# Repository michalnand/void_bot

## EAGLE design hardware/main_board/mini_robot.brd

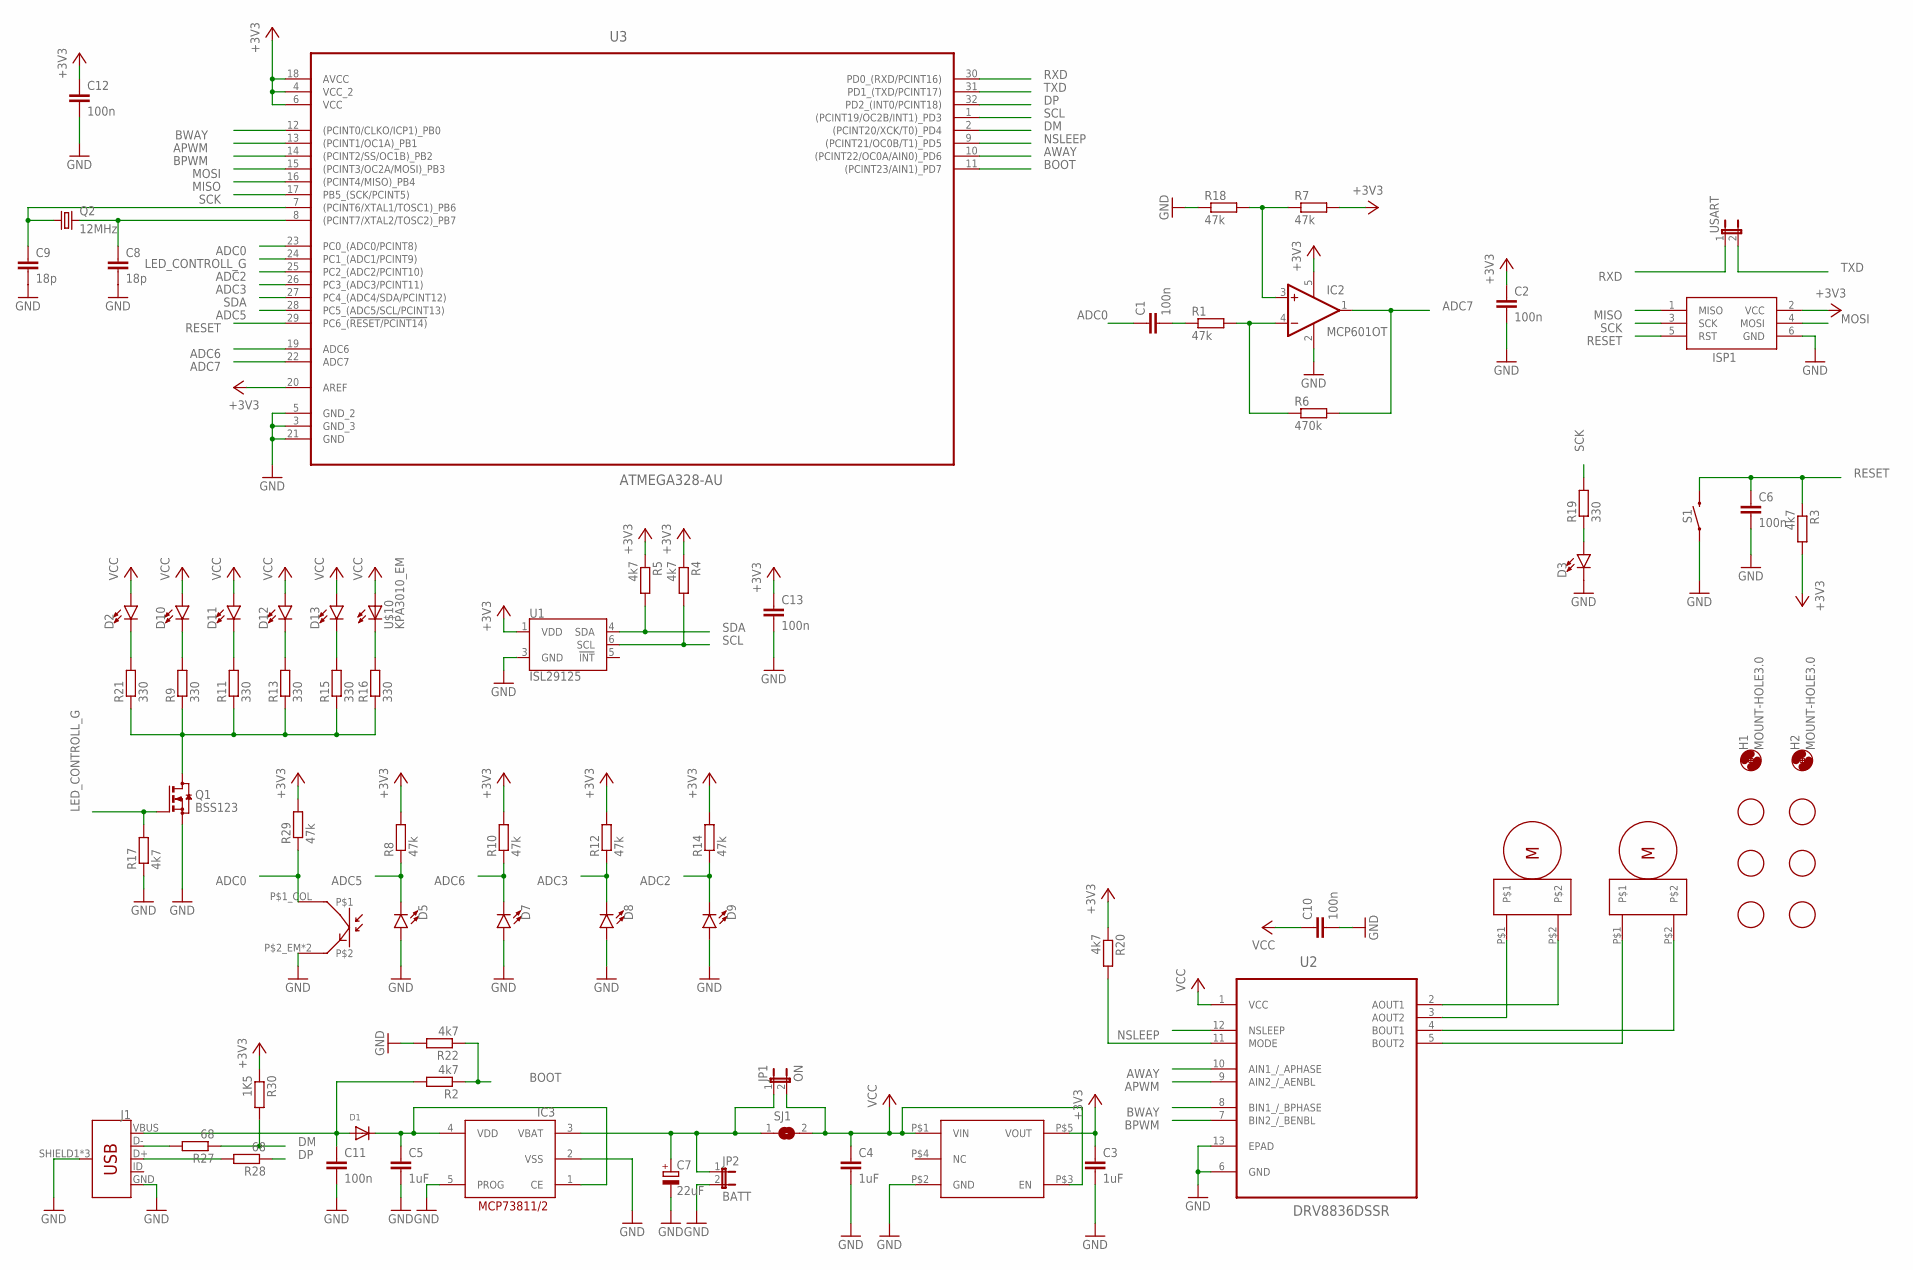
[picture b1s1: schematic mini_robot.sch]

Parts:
C1, C2, C6, C10, C11, C12, C13: 100n; C0603
C3, C4: 1uF; C0805
C5: 1uF; C0603
C7: 22uF; 153CLV-0505
C8, C9: 18p; C0603
D1: DIODE_SOD-123FL; SOD-123FL
D2, D3, D5, D7, D8, D9, D10, D11, D12, D13: LED-FKIT-1206; FKIT-LED-1206
H1, H2: MOUNT-HOLE3.0; 3,0
IC2: MCP601OT; SOT23-5
IC3: MCP73811/2; SOT23-5L
ISP1: AVRISP-6; AVRISP
J1: USB_MICRO-B_FEMALE-SMT; USB-B-MICRO-SMD
JP1: ON; JP1
JP2: BATT; JP1
Q1: BSS123; SOT23
Q2: 12MHz; CTS406
R1, R7, R8, R10, R12, R14, R18, R29: 47k; R0603
R2, R3, R4, R5, R17, R20, R22: 4k7; R0603
R6: 470k; R0603
R9, R11, R13, R15, R16, R19, R21: 330; R0603
R27, R28: 68; R0603
R30: 1K5; R0603
S1: MOMENTARY-SWITCH-SPST-SMD-6.2MM-TALL; TACTILE_SWITCH_SMD_6.2MM_TALL
SJ1: SJ
U1: ISL29125; ODFN-6
U2: DRV8836DSSR; SON50P200X300X80-13N
U3: ATMEGA328-AU; QFP80P900X900X120-32N
U$1, U$3, U$4, U$5, U$6, U$7: FIDUCIAL; FIDUCIAL_1MM
U$2: KPA3010
U$8, U$9: PLANETARY_GEAR_MOTOR
U$10: KPA3010_EM; KPA3010
U$11: MIC5504-3.3Y; SOT23-5
USART: JP1E; JP1

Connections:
+3V3: C2.1, C3.1, C12.1, C13.1, IC2.5 (V+), ISP1.2 (VCC), R3.2, R4.1, R5.1, R7.2, R8.2, R10.2, R12.2, R14.2, R20.1, R29.2, R30.1, U1.1 (VDD), U3.4 (VCC_2), U3.6 (VCC), U3.18 (AVCC), U3.20 (AREF), U$11.P$5 (VOUT)
ADC0: C1.1, R29.1, U3.23 (PC0_(ADC0/PCINT8)), U$2.P$1_COL
ADC2: D9.C, R14.1, U3.25 (PC2_(ADC2/PCINT10))
ADC3: D8.C, R12.1, U3.26 (PC3_(ADC3/PCINT11))
ADC5: D5.C, R8.1, U3.28 (PC5_(ADC5/SCL/PCINT13))
ADC6: D7.C, R10.1, U3.19 (ADC6)
ADC7: IC2.1 (OUT), R6.2, U3.22 (ADC7)
APWM: U2.9 (AIN2_/_AENBL), U3.13 ((PCINT1/OC1A)_PB1)
AWAY: U2.10 (AIN1_/_APHASE), U3.10 ((PCINT22/OC0A/AIN0)_PD6)
BOOT: R2.1, R22.1, U3.11 ((PCINT23/AIN1)_PD7)
BPWM: U2.7 (BIN2_/_BENBL), U3.14 ((PCINT2/SS/OC1B)_PB2)
BWAY: U2.8 (BIN1_/_BPHASE), U3.12 ((PCINT0/CLKO/ICP1)_PB0)
DM: R27.1, R30.2, U3.2 ((PCINT20/XCK/T0)_PD4)
DP: R28.1, U3.32 (PD2_(INT0/PCINT18))
GND: C2.2, C3.2, C4.2, C5.2, C6.2, C7.-, C8.2, C9.2, C10.2, C11.2, C12.2, C13.2, D3.C, D5.A, D7.A, D8.A, D9.A, IC2.2 (V-), IC3.2 (VSS), IC3.5 (PROG), ISP1.6 (GND), J1.GND, J1.SHIELD1 (SHIELD), J1.SHIELD2 (SHIELD), J1.SHIELD3 (SHIELD), JP2.2, Q1.2 (S), R17.1, R18.1, R22.2, S1.A2 (1), U1.3 (GND), U2.6 (GND), U2.13 (EPAD), U3.3 (GND_3), U3.5 (GND_2), U3.21 (GND), U$2.P$2_EM, U$2.P$3-NC, U$11.P$2 (GND)
LED_CONTROLL: Q1.3 (D), R9.1, R11.1, R13.1, R15.1, R16.1, R21.1
LED_CONTROLL_G: Q1.1 (G), R17.2, U3.24 (PC1_(ADC1/PCINT9))
MISO: ISP1.1 (MISO), U3.16 ((PCINT4/MISO)_PB4)
MOSI: ISP1.4 (MOSI), U3.15 ((PCINT3/OC2A/MOSI)_PB3)
unnamed: U2.2 (AOUT1), U$8.P$2
unnamed: U2.3 (AOUT2), U$8.P$1
unnamed: U2.4 (BOUT1), U$9.P$2
unnamed: U2.5 (BOUT2), U$9.P$1
unnamed: C11.1, D1.A, J1.VBUS, R2.2
unnamed: C5.1, D1.C, IC3.1 (CE), IC3.4 (VDD)
unnamed: C1.2, R1.1
unnamed: C7.+, IC3.3 (VBAT), JP1.1, JP2.1, SJ1.1
unnamed: R20.2, U2.11 (MODE)
unnamed: D10.C, R9.2
unnamed: D11.C, R11.2
unnamed: D12.C, R13.2
unnamed: D13.C, R15.2
unnamed: R16.2, U$10.P$1_COL (C)
unnamed: C8.1, Q2.3 (2), U3.8 ((PCINT7/XTAL2/TOSC2)_PB7)
unnamed: C9.1, Q2.1, U3.7 ((PCINT6/XTAL1/TOSC1)_PB6)
unnamed: D3.A, R19.1
unnamed: IC2.3 (+IN), R7.1, R18.2
unnamed: IC2.4 (-IN), R1.2, R6.1
unnamed: D2.C, R21.2
unnamed: J1.D-, R27.2
unnamed: J1.D+, R28.2
NSLEEP: U2.12 (NSLEEP), U3.9 ((PCINT21/OC0B/T1)_PD5)
RESET: C6.1, ISP1.5 (RST), R3.1, S1.B2 (2), U3.29 (PC6_(!RESET/PCINT14))
RXD: U3.30 (PD0_(RXD/PCINT16)), USART.1
SCK: ISP1.3 (SCK), R19.2, U3.17 (PB5_(SCK/PCINT5))
SCL: R4.2, U1.6 (SCL), U3.1 ((PCINT19/OC2B/INT1)_PD3)
SDA: R5.2, U1.4 (SDA), U3.27 (PC4_(ADC4/SDA/PCINT12))
TXD: U3.31 (PD1_(TXD/PCINT17)), USART.2
VCC: C4.1, C10.1, D2.A, D10.A, D11.A, D12.A, D13.A, JP1.2, SJ1.2, U2.1 (VCC), U$10.P$2_EM (A), U$10.P$3-NC (A), U$11.P$1 (VIN), U$11.P$3 (EN)

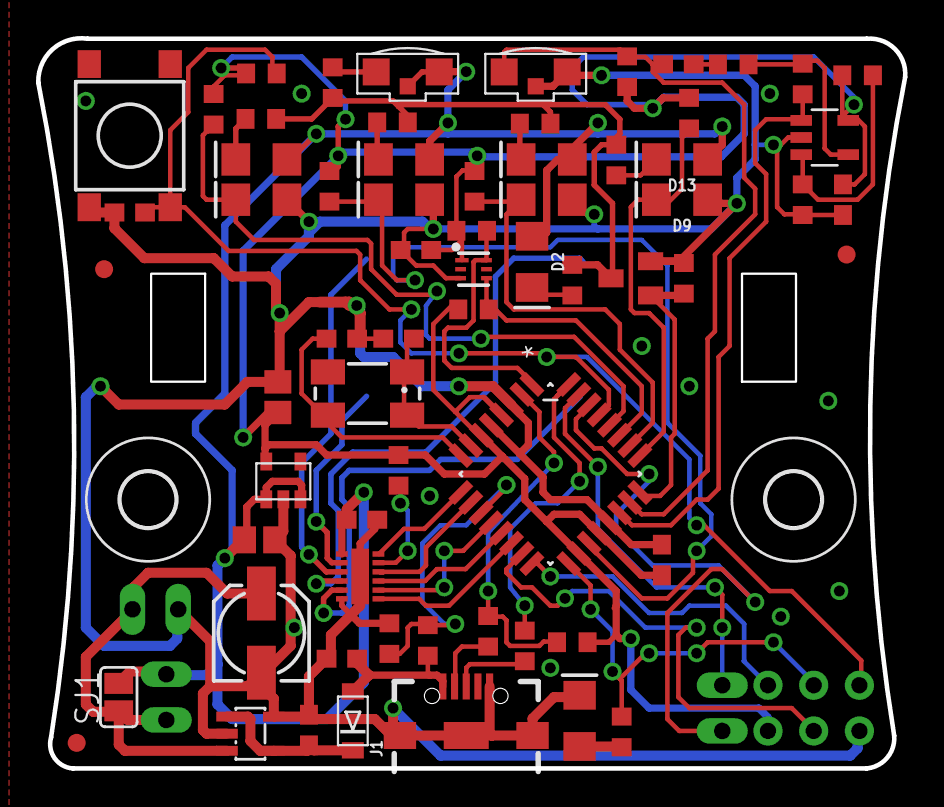
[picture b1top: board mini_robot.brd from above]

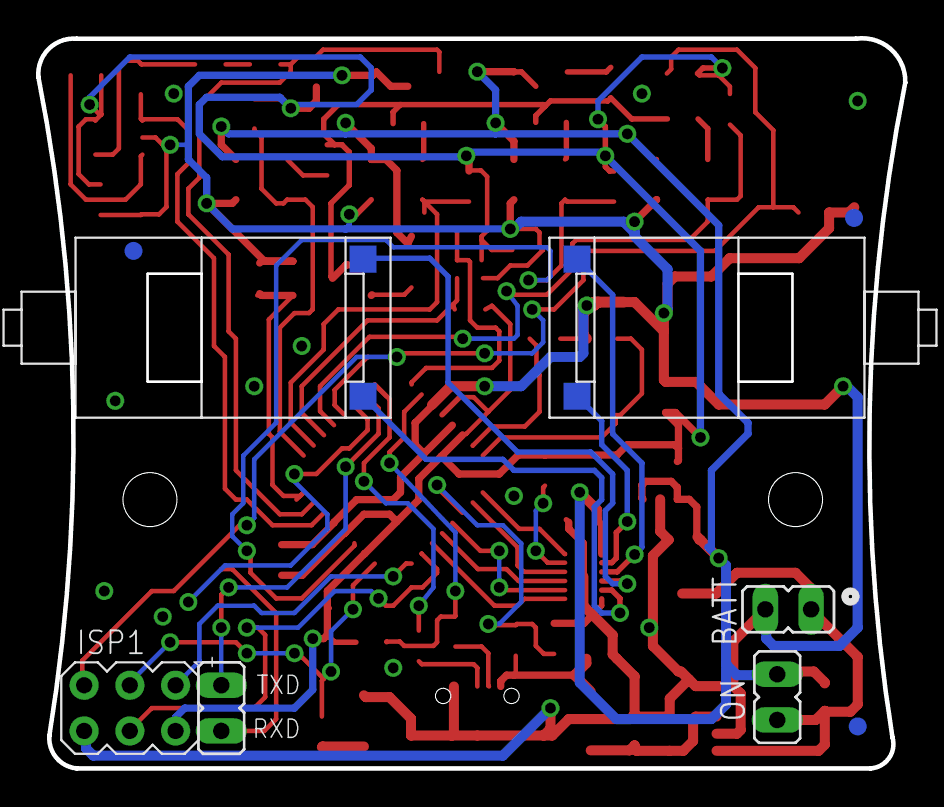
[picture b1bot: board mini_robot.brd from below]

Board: 2 copper layers, 48.2 x 40.6 mm, 77 parts (9 on the bottom side), 49 nets.

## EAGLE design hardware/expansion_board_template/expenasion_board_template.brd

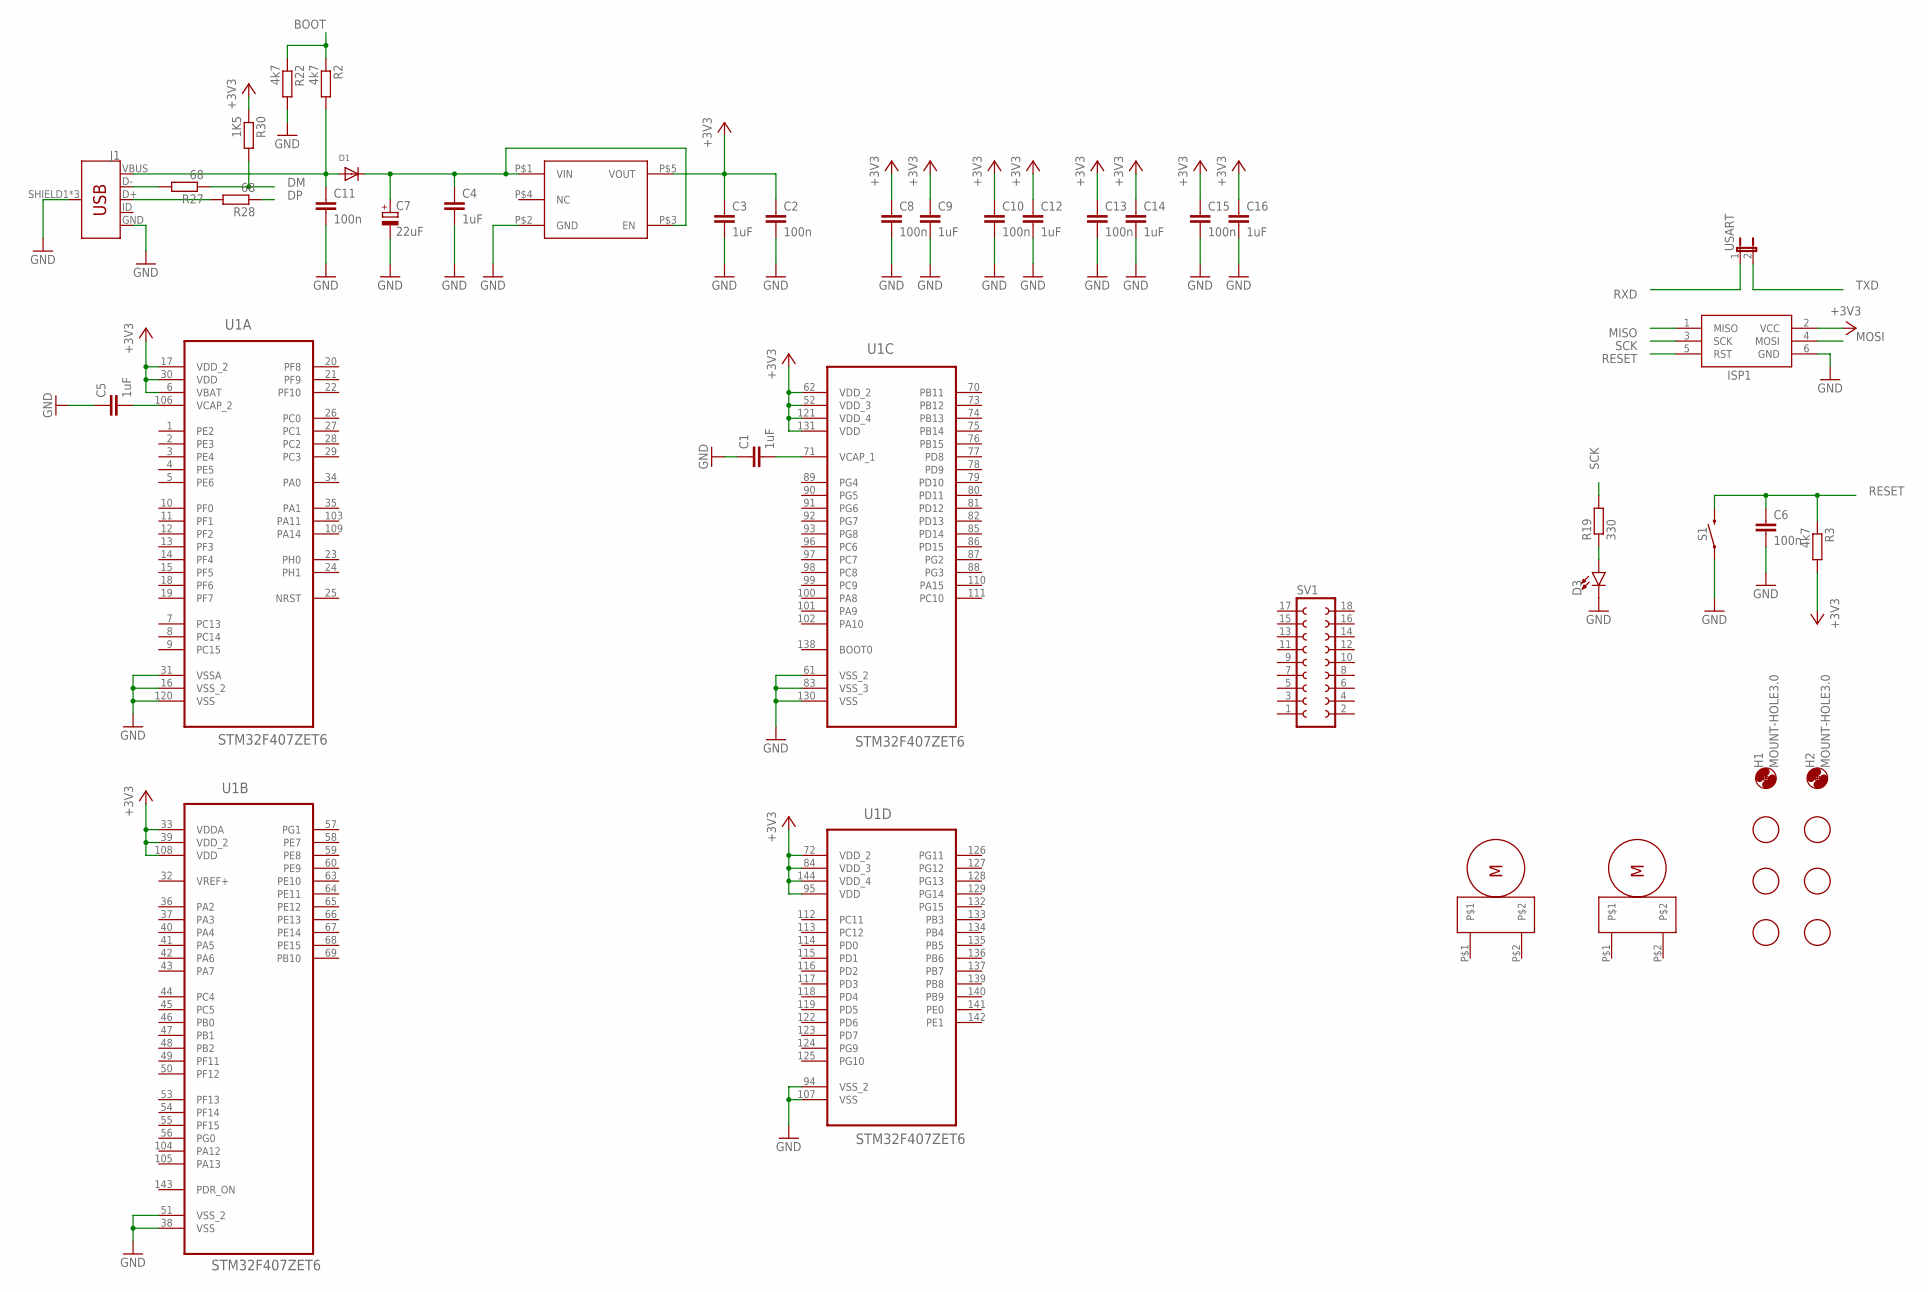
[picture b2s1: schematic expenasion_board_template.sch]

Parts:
C1, C3, C4, C5, C9, C12, C14, C16: 1uF; C0805
C2, C6, C8, C10, C11, C13, C15: 100n; C0603
C7: 22uF; 153CLV-0505
D1: DIODE_SOD-123FL; SOD-123FL
D3: LED-FKIT-1206; FKIT-LED-1206
H1, H2: MOUNT-HOLE3.0; 3,0
ISP1: AVRISP-6; AVRISP
J1: USB_MICRO-B_FEMALE-SMT; USB-B-MICRO-SMD
R2, R3, R22: 4k7; R0603
R19: 330; R0603
R27, R28: 68; R0603
R30: 1K5; R0603
S1: MOMENTARY-SWITCH-SPST-SMD-6.2MM-TALL; TACTILE_SWITCH_SMD_6.2MM_TALL
SV1: FE09-2
U1: STM32F407ZET6; QFP50P2000X2000X160-144N
U$1, U$3, U$4, U$5, U$6, U$7: FIDUCIAL; FIDUCIAL_1MM
U$2, U$10: PLANETARY_GEAR_MOTOR
U$11: MIC5504-3.3Y; SOT23-5
USART: JP1E; JP1

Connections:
+3V3: C2.1, C3.1, C8.1, C9.1, C10.1, C12.1, C13.1, C14.1, C15.1, C16.1, ISP1.2 (VCC), R3.2, R30.1, U1.6 (VBAT), U1.17 (VDD_2), U1.30 (VDD), U1.33 (VDDA), U1.39 (VDD_2), U1.52 (VDD_3), U1.62 (VDD_2), U1.72 (VDD_2), U1.84 (VDD_3), U1.95 (VDD), U1.108 (VDD), U1.121 (VDD_4), U1.131 (VDD), U1.144 (VDD_4), U$11.P$5 (VOUT)
BOOT: R2.1, R22.1
DM: R27.1, R30.2
DP: R28.1
GND: C1.1, C2.2, C3.2, C4.2, C5.1, C6.2, C7.-, C8.2, C9.2, C10.2, C11.2, C12.2, C13.2, C14.2, C15.2, C16.2, D3.C, ISP1.6 (GND), J1.GND, J1.SHIELD1 (SHIELD), J1.SHIELD2 (SHIELD), J1.SHIELD3 (SHIELD), R22.2, S1.A2 (1), U1.16 (VSS_2), U1.31 (VSSA), U1.38 (VSS), U1.51 (VSS_2), U1.61 (VSS_2), U1.83 (VSS_3), U1.94 (VSS_2), U1.107 (VSS), U1.120 (VSS), U1.130 (VSS), U$11.P$2 (GND)
MISO: ISP1.1 (MISO)
MOSI: ISP1.4 (MOSI)
unnamed: C1.2, U1.71 (VCAP_1)
unnamed: C5.2, U1.106 (VCAP_2)
unnamed: C11.1, D1.A, J1.VBUS, R2.2
unnamed: C4.1, C7.+, D1.C, U$11.P$1 (VIN), U$11.P$3 (EN)
unnamed: D3.A, R19.1
unnamed: J1.D-, R27.2
unnamed: J1.D+, R28.2
RESET: C6.1, ISP1.5 (RST), R3.1, S1.B2 (2)
RXD: USART.1
SCK: ISP1.3 (SCK), R19.2
TXD: USART.2
VREF+: U1.32 (VREF+)

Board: 2 copper layers, 42 parts (24 on the bottom side), 13 nets, no tracks yet.

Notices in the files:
parts and their libraries:
SparkFun-Connectors: Licensing: Creative Commons ShareAlike 4.0 International - https://creativecommons.org/licenses/by-sa/4.0
